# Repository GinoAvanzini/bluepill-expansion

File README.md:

# bluepill-expansion
Simple blue pill expansion board. Used as learning tool in a KiCad workshop

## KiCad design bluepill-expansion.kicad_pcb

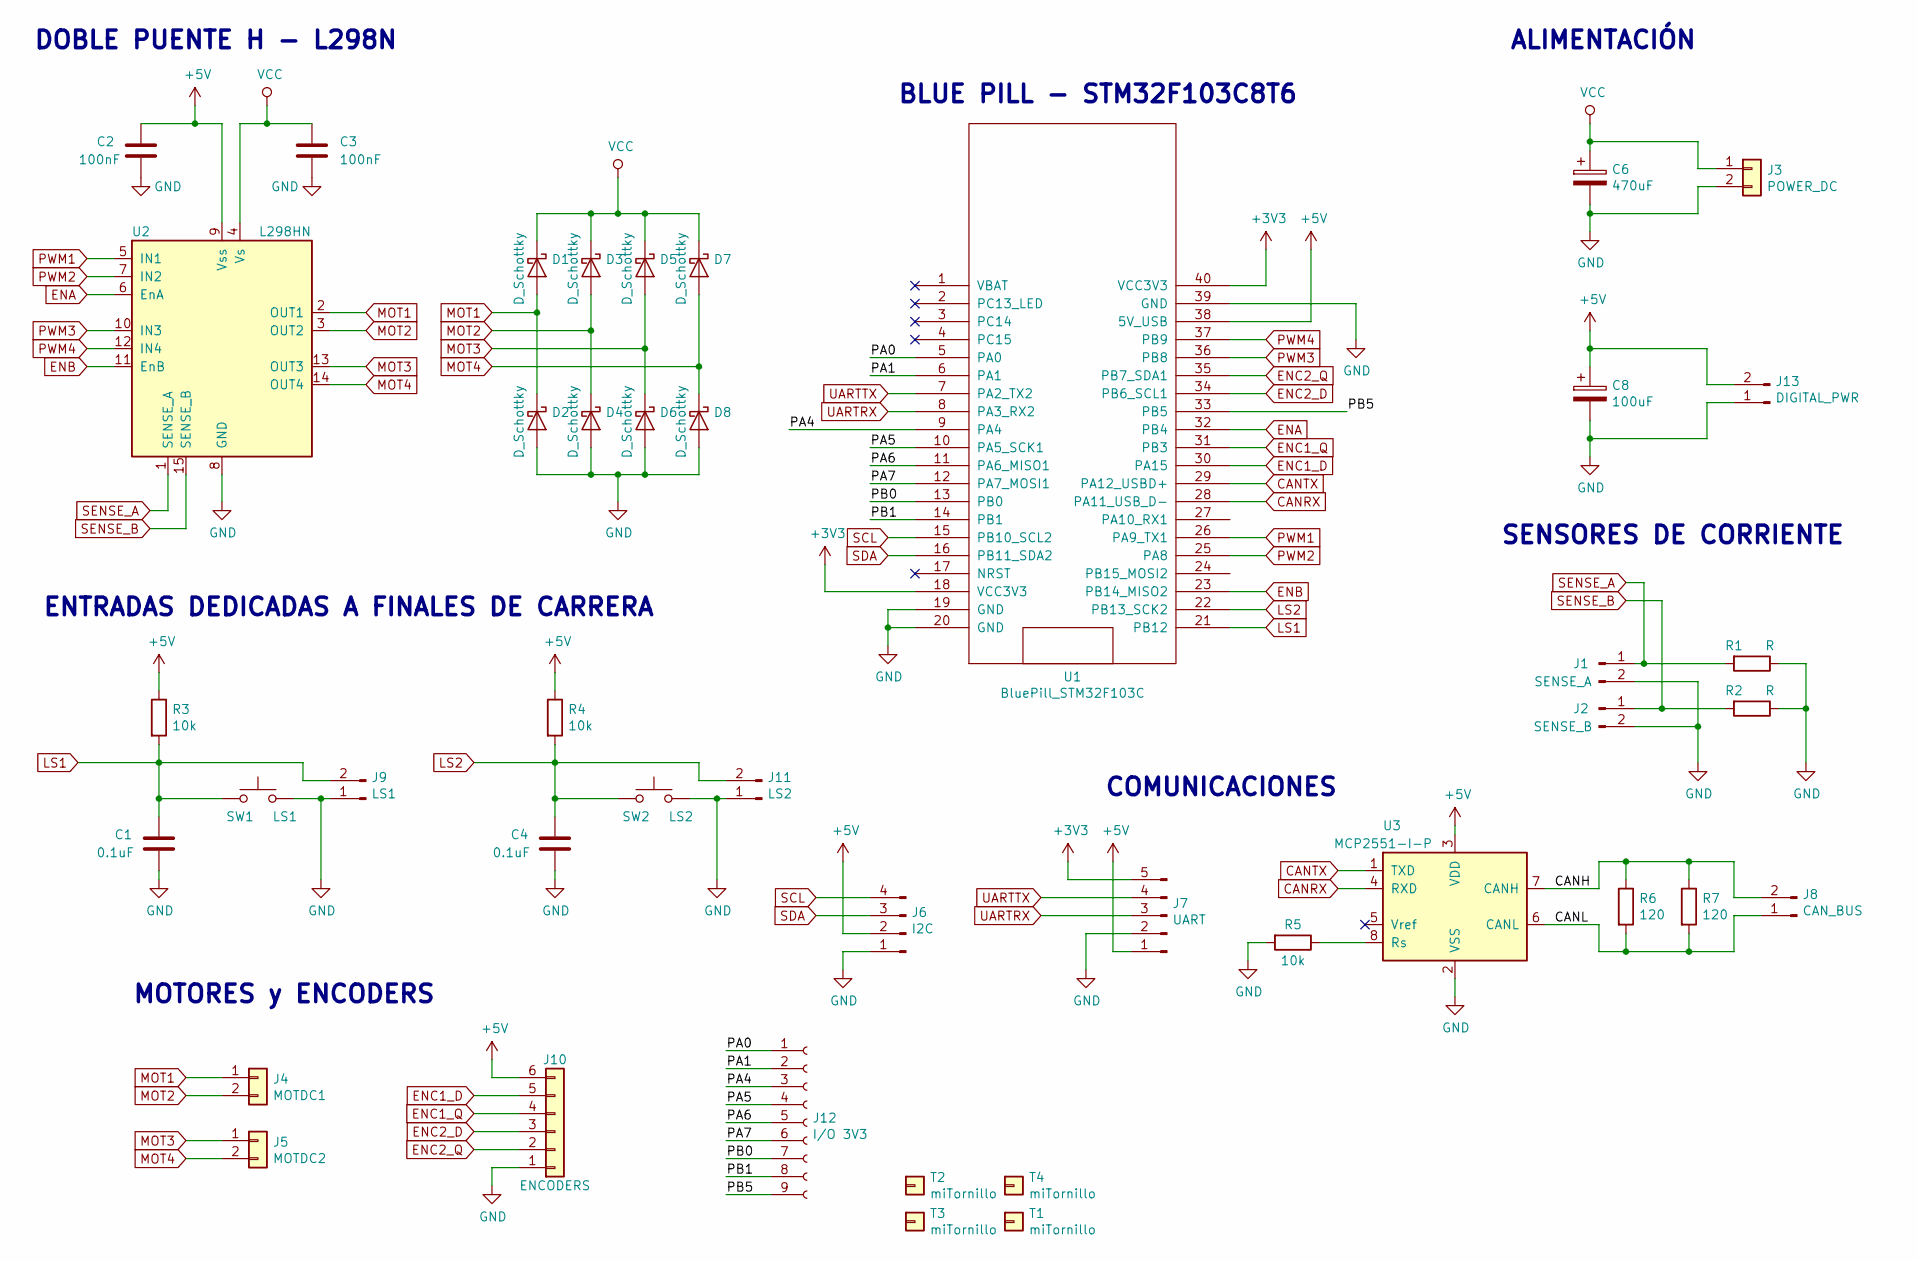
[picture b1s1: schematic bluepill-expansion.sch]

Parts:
C1, C4: 0.1uF; C_Disc_D7.5mm_W2.5mm_P5.00mm
C2, C3: 100nF; C_Disc_D7.5mm_W2.5mm_P5.00mm
C6: 470uF; CP_Radial_D5.0mm_P2.50mm
C8: 100uF; CP_Radial_D5.0mm_P2.50mm
D1, D2, D3, D4, D5, D6, D7, D8: D_Schottky; D_DO-41_SOD81_P12.70mm_Horizontal
J1: SENSE_A; PinHeader_1x02_P2.54mm_Vertical
J2: SENSE_B; PinHeader_1x02_P2.54mm_Vertical
J3: POWER_DC; TerminalBlock_bornier-2_P5.08mm
J4: MOTDC1; TerminalBlock_bornier-2_P5.08mm
J5: MOTDC2; TerminalBlock_bornier-2_P5.08mm
J6: I2C; PinHeader_1x04_P2.54mm_Vertical
J7: UART; PinHeader_1x05_P2.54mm_Vertical
J8: CAN_BUS; PinHeader_1x02_P2.54mm_Vertical
J9: LS1; PinHeader_1x02_P2.54mm_Vertical
J10: ENCODERS; TerminalBlock_bornier-6_P5.08mm
J11: LS2; PinHeader_1x02_P2.54mm_Vertical
J12: I/O 3V3; PinSocket_1x09_P2.54mm_Vertical
J13: DIGITAL_PWR; TerminalBlock_bornier-2_P5.08mm
R1, R2: R; R_Box_L26.0mm_W5.0mm_P20.00mm
R3, R4, R5: 10k; R_Axial_DIN0207_L6.3mm_D2.5mm_P10.16mm_Horizontal
R6, R7: 120; R_Axial_DIN0207_L6.3mm_D2.5mm_P2.54mm_Vertical
SW1: LS1; SW_PUSH_6mm_H7.3mm
SW2: LS2; SW_PUSH_6mm_H7.3mm
T1, T2, T3, T4: miTornillo; M3
U1: BluePill_STM32F103C
U2: L298HN; TO-220-15_P2.54x2.54mm_StaggerOdd_Lead4.58mm_Vertical
U3: MCP2551-I-P; DIP-8_W7.62mm

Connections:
+3V3: J7.5, U1.18 (VCC3V3), U1.40 (VCC3V3)
+5V: C2.1, C8.1, J6.2, J7.1, J10.6, J13.2, R3.1, R4.1, U1.38 (5V_USB), U2.9 (Vss), U3.3 (VDD)
/CANH: J8.2, R6.1, R7.1, U3.7 (CANH)
/CANL: J8.1, R6.2, R7.2, U3.6 (CANL)
/PA0: J12.1, U1.5 (PA0)
/PA1: J12.2, U1.6 (PA1)
/PA4: J12.3, U1.9 (PA4)
/PA5: J12.4, U1.10 (PA5_SCK1)
/PA6: J12.5, U1.11 (PA6_MISO1)
/PA7: J12.6, U1.12 (PA7_MOSI1)
/PB0: J12.7, U1.13 (PB0)
/PB1: J12.8, U1.14 (PB1)
/PB5: J12.9, U1.33 (PB5)
CANRX: U1.28 (PA11_USB_D-), U3.4 (RXD)
CANTX: U1.29 (PA12_USBD+), U3.1 (TXD)
ENA: U1.32 (PB4), U2.6 (EnA)
ENB: U1.23 (PB14_MISO2), U2.11 (EnB)
ENC1_D: J10.5, U1.30 (PA15)
ENC1_Q: J10.4, U1.31 (PB3)
ENC2_D: J10.3, U1.34 (PB6_SCL1)
ENC2_Q: J10.2, U1.35 (PB7_SDA1)
GND: C1.2, C2.2, C3.2, C4.2, C6.2, C8.2, D2.2 (A), D4.2 (A), D6.2 (A), D8.2 (A), J1.2, J2.2, J3.2, J6.1, J7.2, J9.1, J10.1, J11.1, J13.1, R1.1, R2.1, R5.2, SW1.2, SW2.2, U1.19 (GND), U1.20 (GND), U1.39 (GND), U2.8 (GND), U3.2 (VSS)
LS1: C1.1, J9.2, R3.2, SW1.1, U1.21 (PB12)
LS2: C4.1, J11.2, R4.2, SW2.1, U1.22 (PB13_SCK2)
MOT1: D1.2 (A), D2.1 (K), J4.1, U2.2 (OUT1)
MOT2: D3.2 (A), D4.1 (K), J4.2, U2.3 (OUT2)
MOT3: D5.2 (A), D6.1 (K), J5.1, U2.13 (OUT3)
MOT4: D7.2 (A), D8.1 (K), J5.2, U2.14 (OUT4)
unnamed: R5.1, U3.8 (Rs)
PWM1: U1.26 (PA9_TX1), U2.5 (IN1)
PWM2: U1.25 (PA8), U2.7 (IN2)
PWM3: U1.36 (PB8), U2.10 (IN3)
PWM4: U1.37 (PB9), U2.12 (IN4)
SCL: J6.4, U1.15 (PB10_SCL2)
SDA: J6.3, U1.16 (PB11_SDA2)
SENSE_A: J1.1, R1.2, U2.1 (SENSE_A)
SENSE_B: J2.1, R2.2, U2.15 (SENSE_B)
UARTRX: J7.3, U1.8 (PA3_RX2)
UARTTX: J7.4, U1.7 (PA2_TX2)
VCC: C3.1, C6.1, D1.1 (K), D3.1 (K), D5.1 (K), D7.1 (K), J3.1, U2.4 (Vs)

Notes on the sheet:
COMUNICACIONES
SENSORES DE CORRIENTE
BLUE PILL - STM32F103C8T6
DOBLE PUENTE H - L298N
ENTRADAS DEDICADAS A FINALES DE CARRERA
ALIMENTACIÓN
MOTORES y ENCODERS

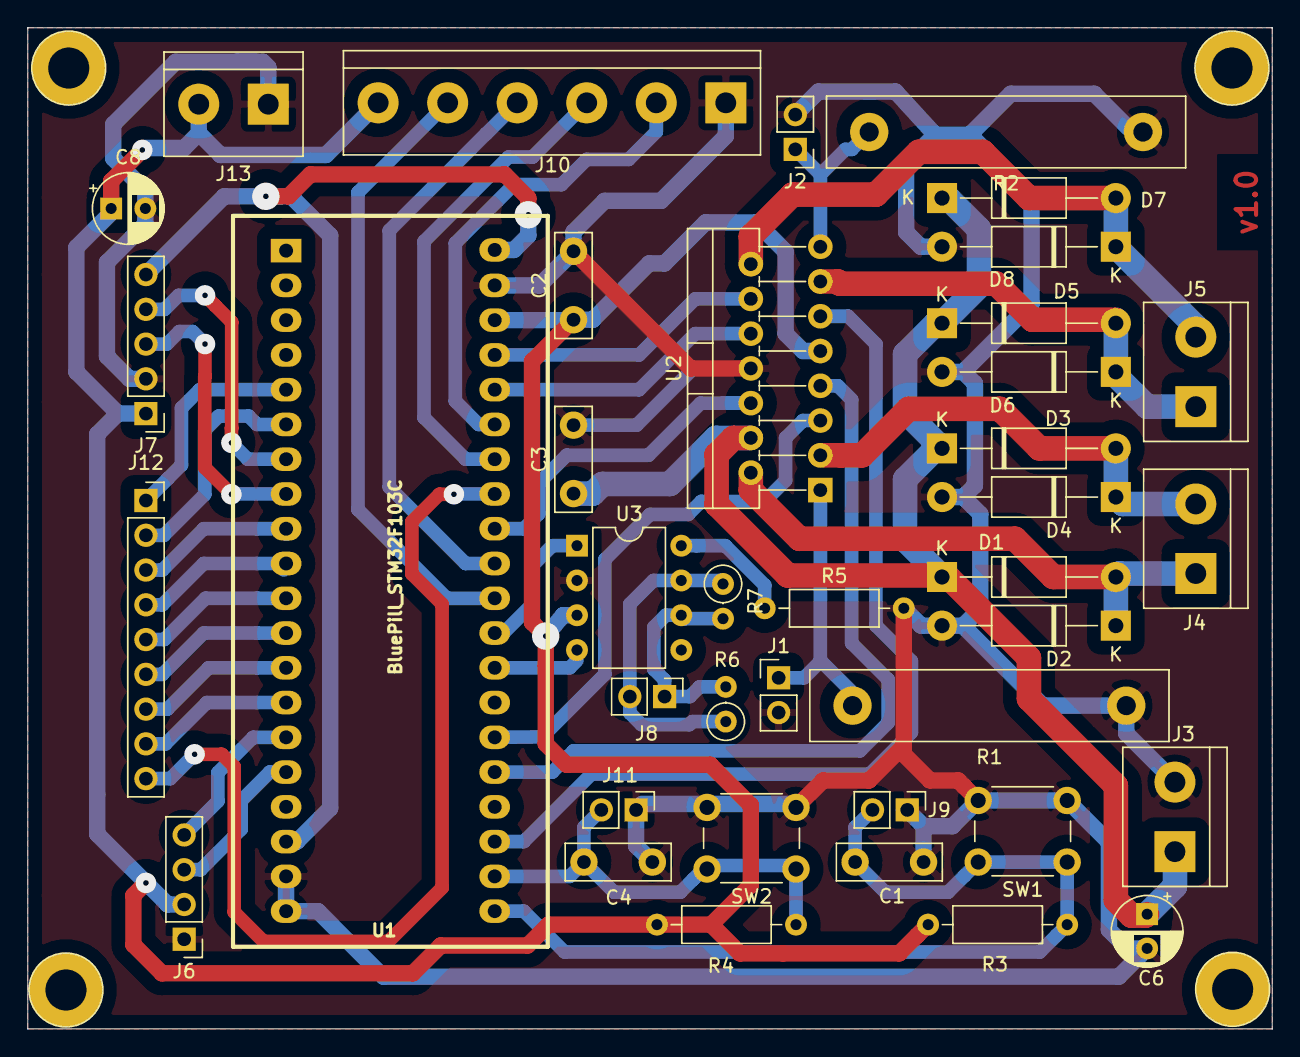
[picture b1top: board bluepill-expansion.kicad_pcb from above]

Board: 2 copper layers, 90.9 x 73.2 mm, 43 parts (0 on the bottom side), 40 nets.

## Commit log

2020-03-02 created kicad project
2020-03-03 project update
2020-03-04 updated schematic
2020-03-04 first routing
2020-03-04 routing update
2020-03-04 final routing sin revisar
2020-03-04 added edge cuts and GND
2020-03-04 added MCP2551 for CAN
2020-03-04 fixed line error
2020-03-06 fixed bluepill symbol
2020-03-07 updated gitignore
2020-03-08 update PCB
2020-03-09 3d fixed
2020-03-09 correct blue pill connection
2020-03-09 cambiosEmma
2020-03-09 CAN R 120
2020-03-10 cambios Emma para enviar a fabricar, orden bus can
